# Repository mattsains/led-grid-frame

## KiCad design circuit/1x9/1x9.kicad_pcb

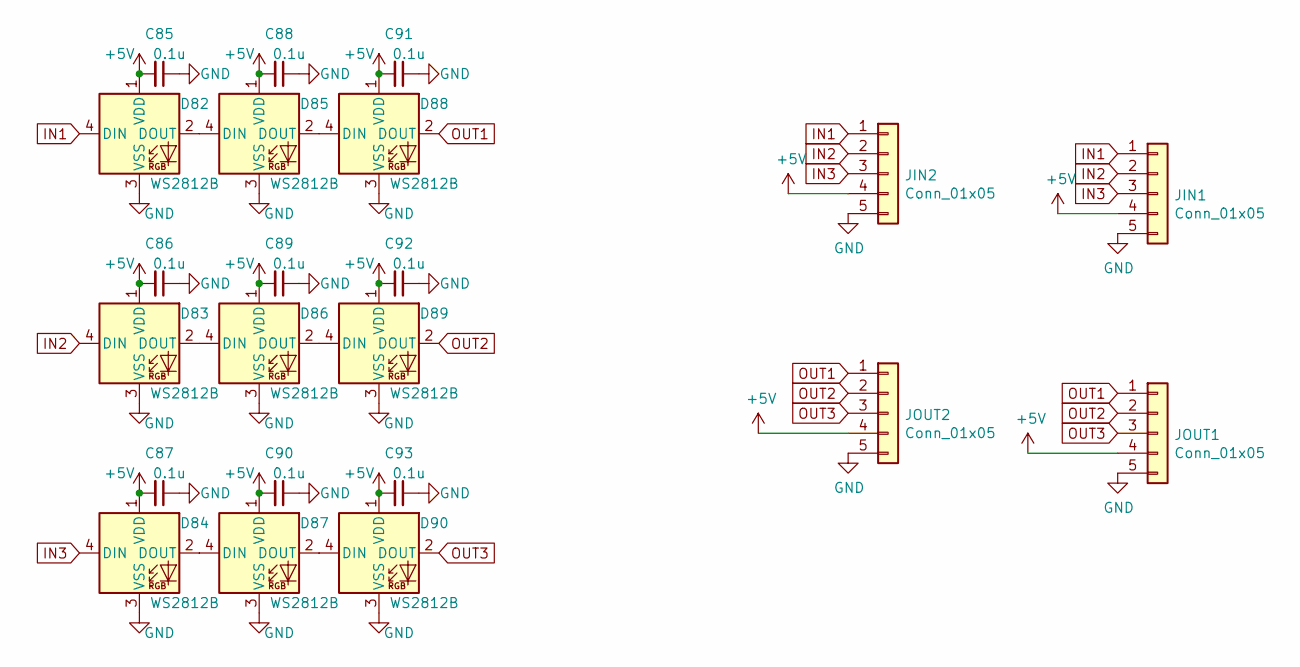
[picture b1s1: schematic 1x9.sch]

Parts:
C85, C86, C87, C88, C89, C90, C91, C92, C93: 0.1u; C_0805_2012Metric
D82, D83, D84, D85, D86, D87, D88, D89, D90: WS2812B; LED_WS2812B_PLCC4_5.0x5.0mm_P3.2mm
JIN1, JIN2: Conn_01x05; thick_header_01x05_3.3mm
JOUT1, JOUT3: Conn_01x05; thick_header_01x05_3.3mm

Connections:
+5V: C85.2, C86.2, C87.2, C88.2, C89.2, C90.2, C91.2, C92.2, C93.2, D82.1 (VDD), D83.1 (VDD), D84.1 (VDD), D85.1 (VDD), D86.1 (VDD), D87.1 (VDD), D88.1 (VDD), D89.1 (VDD), D90.1 (VDD), JIN1.4, JIN2.4, JOUT1.4; also elsewhere on the board
GND: C85.1, C86.1, C87.1, C88.1, C89.1, C90.1, C91.1, C92.1, C93.1, D82.3 (VSS), D83.3 (VSS), D84.3 (VSS), D85.3 (VSS), D86.3 (VSS), D87.3 (VSS), D88.3 (VSS), D89.3 (VSS), D90.3 (VSS), JIN1.5, JIN2.5, JOUT1.5; also elsewhere on the board
IN1: D82.4 (DIN), JIN1.1, JIN2.1
IN2: D83.4 (DIN), JIN1.2, JIN2.2
IN3: D84.4 (DIN), JIN1.3, JIN2.3
unnamed: D82.2 (DOUT), D85.4 (DIN)
unnamed: D83.2 (DOUT), D86.4 (DIN)
unnamed: D84.2 (DOUT), D87.4 (DIN)
unnamed: D85.2 (DOUT), D88.4 (DIN)
unnamed: D86.2 (DOUT), D89.4 (DIN)
unnamed: D87.2 (DOUT), D90.4 (DIN)
OUT1: D88.2 (DOUT), JOUT1.1; also elsewhere on the board
OUT2: D89.2 (DOUT), JOUT1.2; also elsewhere on the board
OUT3: D90.2 (DOUT), JOUT1.3; also elsewhere on the board

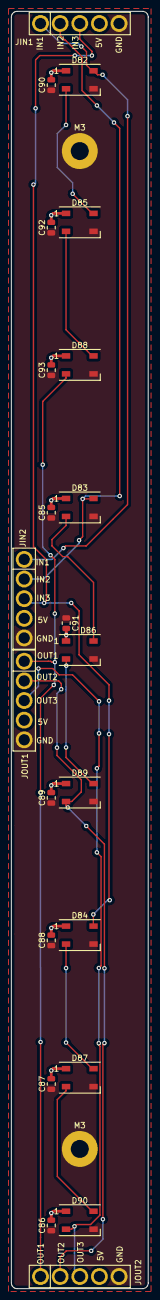
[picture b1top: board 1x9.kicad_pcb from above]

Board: 2 copper layers, 24.4 x 227.6 mm, 24 parts (0 on the bottom side), 14 nets.

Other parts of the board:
JOUT2: Conn_01x05; thick_header_01x05_3.3mm
M3, M3#2: MountingHole_3.2mm_M3_Pad

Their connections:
+5V: JOUT2.4; also elsewhere on the board
GND: JOUT2.5, M3.1, M3#2.1; also elsewhere on the board
OUT1: JOUT2.1; also elsewhere on the board
OUT2: JOUT2.2; also elsewhere on the board
OUT3: JOUT2.3; also elsewhere on the board

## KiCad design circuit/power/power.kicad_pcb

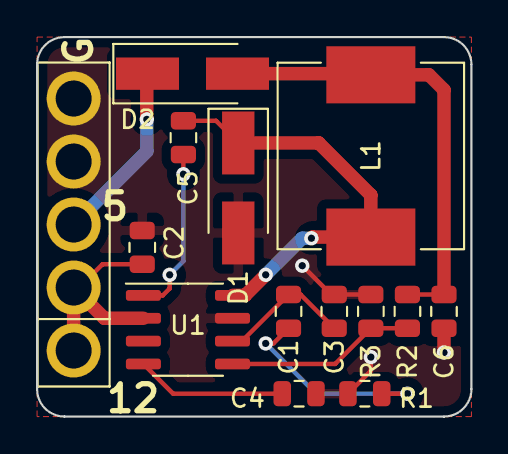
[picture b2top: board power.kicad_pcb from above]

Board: 2 copper layers, 24.1 x 21.1 mm, 14 parts (0 on the bottom side), 10 nets.

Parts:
C1: 1800p; C_0805_2012Metric
C2: 10u; C_0805_2012Metric
C3: 68p; C_0805_2012Metric
C4: 0.015u; C_0805_2012Metric
C5: 0.1u; C_0805_2012Metric
C6: 47u; C_0805_2012Metric
D1, D2: B240A; D_SMA_Handsoldering
JIN1: Conn_01x05; thick_header_01x05_3.3mm
L1: 22u; L_Vishay_IHLP-4040
R1: 21k; R_0805_2012Metric
R2: 10k; R_0805_2012Metric
R3: 1.91k; R_0805_2012Metric
U1: TPS54233; SOIC-8_3.9x4.9mm_P1.27mm

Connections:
+5V: D2.1, JIN1.3
+12V: C2.1, JIN1.1, JIN1.2, U1.2
GND: C2.2, C3.2, C4.2, C6.2, D1.2, JIN1.4, JIN1.5, R1.2, R3.2, U1.7
unnamed: C1.1, C3.1, U1.6
unnamed: C1.2, R1.1
unnamed: C4.1, U1.4
unnamed: C5.1, D1.1, L1.1, U1.8
unnamed: C5.2, U1.1
unnamed: C6.1, D2.2, L1.2, R2.1
unnamed: R2.2, R3.1, U1.5

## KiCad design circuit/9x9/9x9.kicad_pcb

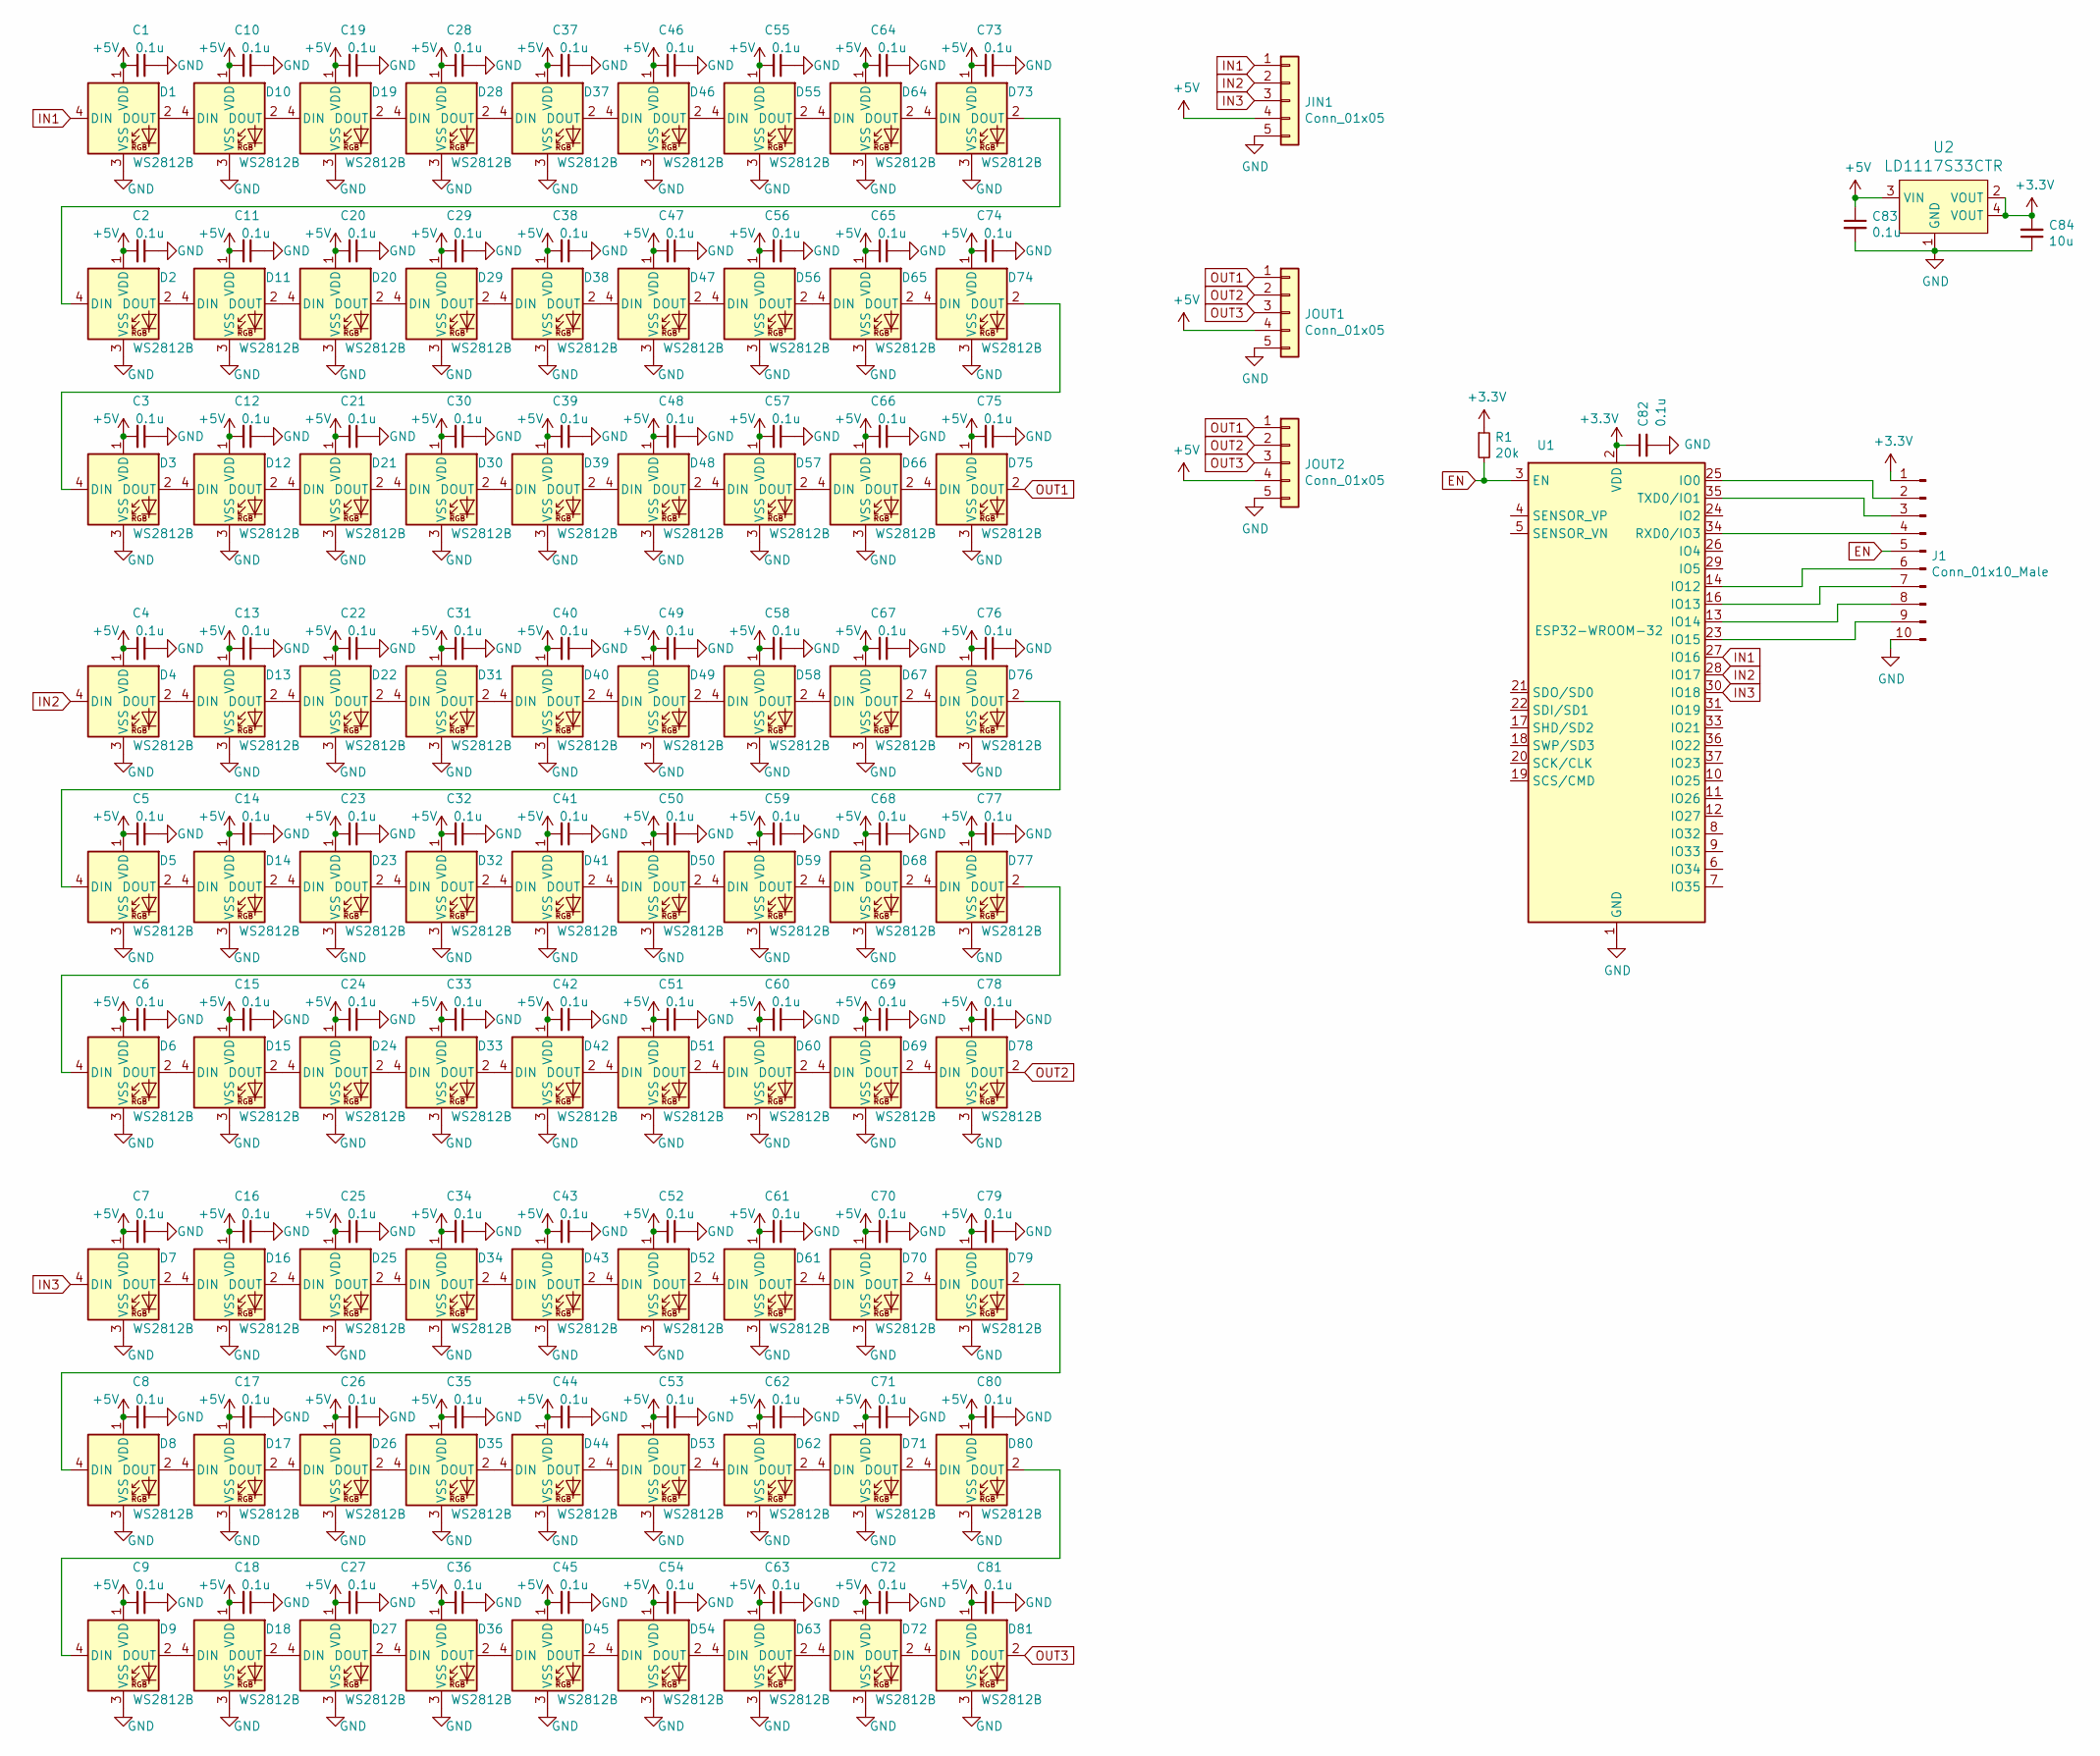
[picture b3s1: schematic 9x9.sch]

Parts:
C1, C2, C3, C4, C5, C6, C7, C8, C9, C10, C11, C12, C13, C14, C15, C16, C17, C18, C19, C20, C21, C22, C23, C24, C25, C26, C27, C28, C29, C30, C31, C32, C33, C34, C35, C36, C37, C38, C39, C40, C41, C42, C43, C44, C45, C46, C47, C48, C49, C50, C51, C52, C53, C54, C55, C56, C57, C58, C59, C60, C61, C62, C63, C64, C65, C66, C67, C68, C69, C70, C71, C72, C73, C74, C75, C76, C77, C78, C79, C80, C81, C82, C83: 0.1u; C_0805_2012Metric
C84: 10u; C_0805_2012Metric
D1, D2, D3, D4, D5, D6, D7, D8, D9, D10, D11, D12, D13, D14, D15, D16, D17, D18, D19, D20, D21, D22, D23, D24, D25, D26, D27, D28, D29, D30, D31, D32, D33, D34, D35, D36, D37, D38, D39, D40, D41, D42, D43, D44, D45, D46, D47, D48, D49, D50, D51, D52, D53, D54, D55, D56, D57, D58, D59, D60, D61, D62, D63, D64, D65, D66, D67, D68, D69, D70, D71, D72, D73, D74, D75, D76, D77, D78, D79, D80, D81: WS2812B; LED_WS2812B_PLCC4_5.0x5.0mm_P3.2mm
J1: Conn_01x10_Male; PinHeader_2x05_P2.54mm_Vertical
JIN1: Conn_01x05; thick_header_01x05_3.3mm
JOUT1, JOUT2: Conn_01x05; thick_header_01x05_3.3mm
R1: 20k; C_1206_3216Metric
U1: ESP32-WROOM-32
U2: LD1117S33CTR; SOT-223; MPN LD1117S33CTR; Digi-Key_PN 497-1241-1-ND

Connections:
+3V3: C82.1, C84.2, J1.1, R1.1, U1.2 (VDD), U2.2 (VOUT), U2.4 (VOUT)
+5V: C1.2, C2.2, C3.2, C4.2, C5.2, C6.2, C7.2, C8.2, C9.2, C10.2, C11.2, C12.2, C13.2, C14.2, C15.2, C16.2, C17.2, C18.2, C19.2, C20.2, C21.2, C22.2, C23.2, C24.2, C25.2, C26.2, C27.2, C28.2, C29.2, C30.2, C31.2, C32.2, C33.2, C34.2, C35.2, C36.2, C37.2, C38.2, C39.2, C40.2, C41.2, C42.2, C43.2, C44.2, C45.2, C46.2, C47.2, C48.2, C49.2, C50.2, C51.2, C52.2, C53.2, C54.2, C55.2, C56.2, C57.2, C58.2, C59.2, C60.2, C61.2, C62.2, C63.2, C64.2, C65.2, C66.2, C67.2, C68.2, C69.2, C70.2, C71.2, C72.2, C73.2, C74.2, C75.2, C76.2, C77.2, C78.2, C79.2, C80.2, C81.2, C83.1, D1.1 (VDD), D2.1 (VDD), D3.1 (VDD), D4.1 (VDD), D5.1 (VDD), D6.1 (VDD), D7.1 (VDD), D8.1 (VDD), D9.1 (VDD), D10.1 (VDD), D11.1 (VDD), D12.1 (VDD), D13.1 (VDD), D14.1 (VDD), D15.1 (VDD), D16.1 (VDD), D17.1 (VDD), D18.1 (VDD), D19.1 (VDD), D20.1 (VDD), D21.1 (VDD), D22.1 (VDD), D23.1 (VDD), D24.1 (VDD), D25.1 (VDD), D26.1 (VDD), D27.1 (VDD), D28.1 (VDD), D29.1 (VDD), D30.1 (VDD), D31.1 (VDD), D32.1 (VDD), D33.1 (VDD), D34.1 (VDD), D35.1 (VDD), D36.1 (VDD), D37.1 (VDD), D38.1 (VDD), D39.1 (VDD), D40.1 (VDD), D41.1 (VDD), D42.1 (VDD), D43.1 (VDD), D44.1 (VDD), D45.1 (VDD), D46.1 (VDD), D47.1 (VDD), D48.1 (VDD), D49.1 (VDD), D50.1 (VDD), D51.1 (VDD), D52.1 (VDD), D53.1 (VDD), D54.1 (VDD), D55.1 (VDD), D56.1 (VDD), D57.1 (VDD), D58.1 (VDD), D59.1 (VDD), D60.1 (VDD), D61.1 (VDD), D62.1 (VDD), D63.1 (VDD), D64.1 (VDD), D65.1 (VDD), D66.1 (VDD), D67.1 (VDD), D68.1 (VDD), D69.1 (VDD), D70.1 (VDD), D71.1 (VDD), D72.1 (VDD), D73.1 (VDD), D74.1 (VDD), D75.1 (VDD), D76.1 (VDD), D77.1 (VDD), D78.1 (VDD), D79.1 (VDD), D80.1 (VDD), D81.1 (VDD), JIN1.4, JOUT1.4, JOUT2.4, U2.3 (VIN)
EN: J1.5, R1.2, U1.3 (EN)
GND: C1.1, C2.1, C3.1, C4.1, C5.1, C6.1, C7.1, C8.1, C9.1, C10.1, C11.1, C12.1, C13.1, C14.1, C15.1, C16.1, C17.1, C18.1, C19.1, C20.1, C21.1, C22.1, C23.1, C24.1, C25.1, C26.1, C27.1, C28.1, C29.1, C30.1, C31.1, C32.1, C33.1, C34.1, C35.1, C36.1, C37.1, C38.1, C39.1, C40.1, C41.1, C42.1, C43.1, C44.1, C45.1, C46.1, C47.1, C48.1, C49.1, C50.1, C51.1, C52.1, C53.1, C54.1, C55.1, C56.1, C57.1, C58.1, C59.1, C60.1, C61.1, C62.1, C63.1, C64.1, C65.1, C66.1, C67.1, C68.1, C69.1, C70.1, C71.1, C72.1, C73.1, C74.1, C75.1, C76.1, C77.1, C78.1, C79.1, C80.1, C81.1, C82.2, C83.2, C84.1, D1.3 (VSS), D2.3 (VSS), D3.3 (VSS), D4.3 (VSS), D5.3 (VSS), D6.3 (VSS), D7.3 (VSS), D8.3 (VSS), D9.3 (VSS), D10.3 (VSS), D11.3 (VSS), D12.3 (VSS), D13.3 (VSS), D14.3 (VSS), D15.3 (VSS), D16.3 (VSS), D17.3 (VSS), D18.3 (VSS), D19.3 (VSS), D20.3 (VSS), D21.3 (VSS), D22.3 (VSS), D23.3 (VSS), D24.3 (VSS), D25.3 (VSS), D26.3 (VSS), D27.3 (VSS), D28.3 (VSS), D29.3 (VSS), D30.3 (VSS), D31.3 (VSS), D32.3 (VSS), D33.3 (VSS), D34.3 (VSS), D35.3 (VSS), D36.3 (VSS), D37.3 (VSS), D38.3 (VSS), D39.3 (VSS), D40.3 (VSS), D41.3 (VSS), D42.3 (VSS), D43.3 (VSS), D44.3 (VSS), D45.3 (VSS), D46.3 (VSS), D47.3 (VSS), D48.3 (VSS), D49.3 (VSS), D50.3 (VSS), D51.3 (VSS), D52.3 (VSS), D53.3 (VSS), D54.3 (VSS), D55.3 (VSS), D56.3 (VSS), D57.3 (VSS), D58.3 (VSS), D59.3 (VSS), D60.3 (VSS), D61.3 (VSS), D62.3 (VSS), D63.3 (VSS), D64.3 (VSS), D65.3 (VSS), D66.3 (VSS), D67.3 (VSS), D68.3 (VSS), D69.3 (VSS), D70.3 (VSS), D71.3 (VSS), D72.3 (VSS), D73.3 (VSS), D74.3 (VSS), D75.3 (VSS), D76.3 (VSS), D77.3 (VSS), D78.3 (VSS), D79.3 (VSS), D80.3 (VSS), D81.3 (VSS), J1.10, JIN1.5, JOUT1.5, JOUT2.5, U1.1 (GND), U1.15 (GND), U1.38 (GND), U2.1 (GND)
IN1: D1.4 (DIN), JIN1.1, U1.27 (IO16)
IN2: D4.4 (DIN), JIN1.2, U1.28 (IO17)
IN3: D7.4 (DIN), JIN1.3, U1.30 (IO18)
unnamed: D1.2 (DOUT), D10.4 (DIN)
unnamed: D2.4 (DIN), D73.2 (DOUT)
unnamed: D3.4 (DIN), D74.2 (DOUT)
unnamed: D5.4 (DIN), D76.2 (DOUT)
unnamed: D6.4 (DIN), D77.2 (DOUT)
unnamed: D10.2 (DOUT), D19.4 (DIN)
unnamed: D11.2 (DOUT), D20.4 (DIN)
unnamed: D2.2 (DOUT), D11.4 (DIN)
unnamed: D12.2 (DOUT), D21.4 (DIN)
unnamed: D3.2 (DOUT), D12.4 (DIN)
unnamed: D13.2 (DOUT), D22.4 (DIN)
unnamed: D4.2 (DOUT), D13.4 (DIN)
unnamed: D14.2 (DOUT), D23.4 (DIN)
unnamed: D5.2 (DOUT), D14.4 (DIN)
unnamed: D15.2 (DOUT), D24.4 (DIN)
unnamed: D6.2 (DOUT), D15.4 (DIN)
unnamed: D16.2 (DOUT), D25.4 (DIN)
unnamed: D7.2 (DOUT), D16.4 (DIN)
unnamed: D17.2 (DOUT), D26.4 (DIN)
unnamed: D8.2 (DOUT), D17.4 (DIN)
unnamed: D18.2 (DOUT), D27.4 (DIN)
unnamed: D9.2 (DOUT), D18.4 (DIN)
unnamed: D19.2 (DOUT), D28.4 (DIN)
unnamed: D20.2 (DOUT), D29.4 (DIN)
unnamed: D21.2 (DOUT), D30.4 (DIN)
unnamed: D22.2 (DOUT), D31.4 (DIN)
unnamed: D23.2 (DOUT), D32.4 (DIN)
unnamed: D24.2 (DOUT), D33.4 (DIN)
unnamed: D25.2 (DOUT), D34.4 (DIN)
unnamed: D26.2 (DOUT), D35.4 (DIN)
unnamed: D27.2 (DOUT), D36.4 (DIN)
unnamed: D28.2 (DOUT), D37.4 (DIN)
unnamed: D29.2 (DOUT), D38.4 (DIN)
unnamed: D30.2 (DOUT), D39.4 (DIN)
unnamed: D31.2 (DOUT), D40.4 (DIN)
unnamed: D32.2 (DOUT), D41.4 (DIN)
unnamed: D33.2 (DOUT), D42.4 (DIN)
unnamed: D34.2 (DOUT), D43.4 (DIN)
unnamed: D35.2 (DOUT), D44.4 (DIN)
unnamed: D36.2 (DOUT), D45.4 (DIN)
unnamed: D37.2 (DOUT), D46.4 (DIN)
unnamed: D38.2 (DOUT), D47.4 (DIN)
unnamed: D39.2 (DOUT), D48.4 (DIN)
unnamed: D40.2 (DOUT), D49.4 (DIN)
unnamed: D41.2 (DOUT), D50.4 (DIN)
unnamed: D42.2 (DOUT), D51.4 (DIN)
unnamed: D43.2 (DOUT), D52.4 (DIN)
unnamed: D44.2 (DOUT), D53.4 (DIN)
unnamed: D45.2 (DOUT), D54.4 (DIN)
unnamed: D46.2 (DOUT), D55.4 (DIN)
unnamed: D47.2 (DOUT), D56.4 (DIN)
unnamed: D48.2 (DOUT), D57.4 (DIN)
unnamed: D49.2 (DOUT), D58.4 (DIN)
unnamed: D50.2 (DOUT), D59.4 (DIN)
unnamed: D51.2 (DOUT), D60.4 (DIN)
unnamed: D52.2 (DOUT), D61.4 (DIN)
unnamed: D53.2 (DOUT), D62.4 (DIN)
unnamed: D54.2 (DOUT), D63.4 (DIN)
unnamed: D55.2 (DOUT), D64.4 (DIN)
unnamed: D56.2 (DOUT), D65.4 (DIN)
unnamed: D57.2 (DOUT), D66.4 (DIN)
unnamed: D58.2 (DOUT), D67.4 (DIN)
unnamed: D59.2 (DOUT), D68.4 (DIN)
unnamed: D60.2 (DOUT), D69.4 (DIN)
unnamed: D61.2 (DOUT), D70.4 (DIN)
unnamed: D62.2 (DOUT), D71.4 (DIN)
unnamed: D63.2 (DOUT), D72.4 (DIN)
unnamed: D64.2 (DOUT), D73.4 (DIN)
unnamed: D65.2 (DOUT), D74.4 (DIN)
unnamed: D66.2 (DOUT), D75.4 (DIN)
unnamed: D67.2 (DOUT), D76.4 (DIN)
unnamed: D68.2 (DOUT), D77.4 (DIN)
unnamed: D69.2 (DOUT), D78.4 (DIN)
unnamed: D70.2 (DOUT), D79.4 (DIN)
unnamed: D71.2 (DOUT), D80.4 (DIN)
unnamed: D72.2 (DOUT), D81.4 (DIN)
unnamed: D8.4 (DIN), D79.2 (DOUT)
unnamed: D9.4 (DIN), D80.2 (DOUT)
unnamed: J1.2, U1.25 (IO0)
unnamed: J1.3, U1.35 (TXD0/IO1)
unnamed: J1.4, U1.34 (RXD0/IO3)
unnamed: J1.6, U1.14 (IO12)
unnamed: J1.7, U1.16 (IO13)
unnamed: J1.8, U1.13 (IO14)
unnamed: J1.9, U1.23 (IO15)
OUT1: D75.2 (DOUT), JOUT1.1, JOUT2.1
OUT2: D78.2 (DOUT), JOUT1.2, JOUT2.2
OUT3: D81.2 (DOUT), JOUT1.3, JOUT2.3

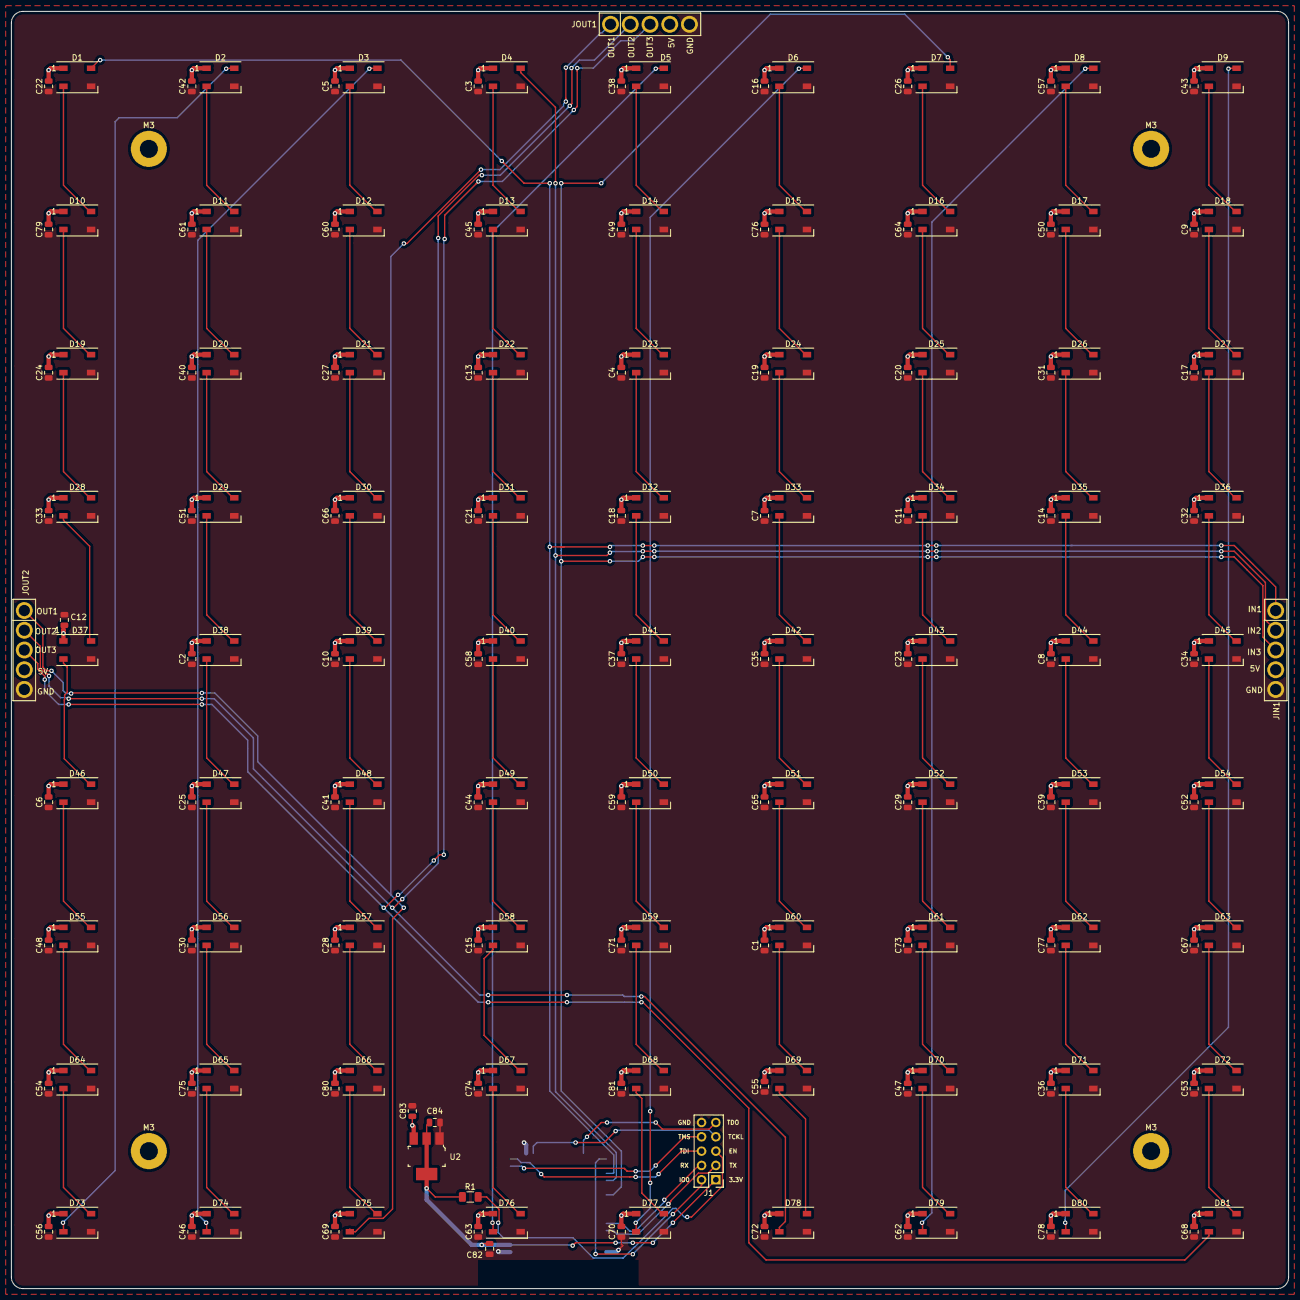
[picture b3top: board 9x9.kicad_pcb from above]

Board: 2 copper layers, 226.6 x 226.6 mm, 176 parts (1 on the bottom side), 95 nets.

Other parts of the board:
M3, M3#2, M3#3, M3#4: MountingHole_3.2mm_M3_Pad

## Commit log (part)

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2020-05-06 v1.1
2020-05-13 snapshot v1.1 and start firmware project
2020-05-16 LED code not working but not crashing either
2020-05-17 LEDs work
2020-05-21 falling rain animation on 9x9!
2020-05-30 18x9 panel
2020-05-30 hacky rain on 19x9
2021-03-06 second layer working
2021-03-06 adding encoder
2021-03-06 color wheel
2021-03-07 working!
2021-03-08 first web UI
2021-03-14 improved client code
2021-03-14 wip: improved firmware stability but still dies occasionally
2021-03-14 ball animation and comments for websocket handler
2021-05-12 Bump postcss from 8.2.7 to 8.2.15 in /client
    Bumps [postcss](https://github.com/postcss/postcss) from 8.2.7 to 8.2.15.
    - [Release notes](https://github.com/postcss/postcss/releases)
    - [Changelog](https://github.com/postcss/postcss/blob/main/CHANGELOG.md)
    - [Commits](https://github.com/postcss/postcss/compare/8.2.7...8.2.15)
2021-05-29 Bump dns-packet from 1.3.1 to 1.3.4 in /client
    Bumps [dns-packet](https://github.com/mafintosh/dns-packet) from 1.3.1 to 1.3.4.
    - [Release notes](https://github.com/mafintosh/dns-packet/releases)
    - [Changelog](https://github.com/mafintosh/dns-packet/blob/master/CHANGELOG.md)
    - [Commits](https://github.com/mafintosh/dns-packet/compare/v1.3.1...v1.3.4)
2021-05-31 Bump ws from 7.4.4 to 7.4.6 in /client
    Bumps [ws](https://github.com/websockets/ws) from 7.4.4 to 7.4.6.
    - [Release notes](https://github.com/websockets/ws/releases)
    - [Commits](https://github.com/websockets/ws/compare/7.4.4...7.4.6)
2021-08-13 Bump path-parse from 1.0.6 to 1.0.7 in /client
    Bumps [path-parse](https://github.com/jbgutierrez/path-parse) from 1.0.6 to 1.0.7.
    - [Release notes](https://github.com/jbgutierrez/path-parse/releases)
    - [Commits](https://github.com/jbgutierrez/path-parse/commits/v1.0.7)
    ---
    updated-dependencies:
    - dependency-name: path-parse
2021-10-06 Bump url-parse from 1.5.1 to 1.5.3 in /client
    Bumps [url-parse](https://github.com/unshiftio/url-parse) from 1.5.1 to 1.5.3.
    - [Release notes](https://github.com/unshiftio/url-parse/releases)
    - [Commits](https://github.com/unshiftio/url-parse/compare/1.5.1...1.5.3)
    ---
    updated-dependencies:
    - dependency-name: url-parse
2021-12-08 it works!
2021-12-08 Displays scrolling emoji
2021-12-12 WIP tetris
2021-12-12 remove bearer token from git
2021-12-13 tetris game 90% there
2021-12-13 typos
2022-02-14 Bump follow-redirects from 1.13.3 to 1.14.8 in /client
    Bumps [follow-redirects](https://github.com/follow-redirects/follow-redirects) from 1.13.3 to 1.14.8.
    - [Release notes](https://github.com/follow-redirects/follow-redirects/releases)
    - [Commits](https://github.com/follow-redirects/follow-redirects/compare/v1.13.3...v1.14.8)
    ---
    updated-dependencies:
    - dependency-name: follow-redirects
2022-02-19 Bump url-parse from 1.5.3 to 1.5.7 in /client
    Bumps [url-parse](https://github.com/unshiftio/url-parse) from 1.5.3 to 1.5.7.
    - [Release notes](https://github.com/unshiftio/url-parse/releases)
    - [Commits](https://github.com/unshiftio/url-parse/compare/1.5.3...1.5.7)
    ---
    updated-dependencies:
    - dependency-name: url-parse
2022-02-26 Bump url-parse from 1.5.7 to 1.5.10 in /client
    Bumps [url-parse](https://github.com/unshiftio/url-parse) from 1.5.7 to 1.5.10.
    - [Release notes](https://github.com/unshiftio/url-parse/releases)
    - [Commits](https://github.com/unshiftio/url-parse/compare/1.5.7...1.5.10)
    ---
    updated-dependencies:
    - dependency-name: url-parse
2022-02-26 Bump browserslist from 4.16.3 to 4.19.3 in /client
    Bumps [browserslist](https://github.com/browserslist/browserslist) from 4.16.3 to 4.19.3.
    - [Release notes](https://github.com/browserslist/browserslist/releases)
    - [Changelog](https://github.com/browserslist/browserslist/blob/main/CHANGELOG.md)
    - [Commits](https://github.com/browserslist/browserslist/compare/4.16.3...4.19.3)
    ---
    updated-dependencies:
2022-02-26 Bump dns-packet from 1.3.1 to 1.3.4 in /client
    Bumps [dns-packet](https://github.com/mafintosh/dns-packet) from 1.3.1 to 1.3.4.
    - [Release notes](https://github.com/mafintosh/dns-packet/releases)
    - [Changelog](https://github.com/mafintosh/dns-packet/blob/master/CHANGELOG.md)
    - [Commits](https://github.com/mafintosh/dns-packet/compare/v1.3.1...v1.3.4)
    ---
    updated-dependencies:
2022-02-26 Bump nanoid from 3.1.20 to 3.3.1 in /client
    Bumps [nanoid](https://github.com/ai/nanoid) from 3.1.20 to 3.3.1.
    - [Release notes](https://github.com/ai/nanoid/releases)
    - [Changelog](https://github.com/ai/nanoid/blob/main/CHANGELOG.md)
    - [Commits](https://github.com/ai/nanoid/compare/3.1.20...3.3.1)
    ---
    updated-dependencies:
2022-03-27 empty app
2022-03-28 first poc game of life
2022-03-29 Bump minimist from 1.2.5 to 1.2.6 in /client
    Bumps [minimist](https://github.com/substack/minimist) from 1.2.5 to 1.2.6.
    - [Release notes](https://github.com/substack/minimist/releases)
    - [Commits](https://github.com/substack/minimist/compare/1.2.5...1.2.6)
    ---
    updated-dependencies:
    - dependency-name: minimist
2022-04-29 Bump async from 2.6.3 to 2.6.4 in /client
    Bumps [async](https://github.com/caolan/async) from 2.6.3 to 2.6.4.
    - [Release notes](https://github.com/caolan/async/releases)
    - [Changelog](https://github.com/caolan/async/blob/v2.6.4/CHANGELOG.md)
    - [Commits](https://github.com/caolan/async/compare/v2.6.3...v2.6.4)
    ---
    updated-dependencies:
2022-07-20 Bump terser from 5.6.0 to 5.14.2 in /client
    Bumps [terser](https://github.com/terser/terser) from 5.6.0 to 5.14.2.
    - [Release notes](https://github.com/terser/terser/releases)
    - [Changelog](https://github.com/terser/terser/blob/master/CHANGELOG.md)
    - [Commits](https://github.com/terser/terser/commits)
    ---
    updated-dependencies:
2022-11-08 Bump loader-utils from 1.4.0 to 1.4.1 in /client
    Bumps [loader-utils](https://github.com/webpack/loader-utils) from 1.4.0 to 1.4.1.
    - [Release notes](https://github.com/webpack/loader-utils/releases)
    - [Changelog](https://github.com/webpack/loader-utils/blob/v1.4.1/CHANGELOG.md)
    - [Commits](https://github.com/webpack/loader-utils/compare/v1.4.0...v1.4.1)
    ---
    updated-dependencies:
2022-11-09 Bump ansi-html and webpack-dev-server in /client
    Removes [ansi-html](https://github.com/Tjatse/ansi-html). It's no longer used after updating ancestor dependency [webpack-dev-server](https://github.com/webpack/webpack-dev-server). These dependencie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
    Removes `ansi-html`
    Updates `webpack-dev-server` from 3.11.2 to 3.11.3
    - [Release notes](https://github.com/webpack/webpack-dev-server/releases)
    - [Changelog](https://github.com/webpack/webpack-dev-server/blob/v3.11.3/CHANGELOG.md)
    - [Commits](https://github.com/webpack/webpack-dev-server/compare/v3.11.2...v3.11.3)
2022-11-09 Bump glob-parent, chokidar and webpack-dev-server in /client
    Bumps [glob-parent](https://github.com/gulpjs/glob-parent) to 5.1.2 and updates ancestor dependencies [glob-parent](https://github.com/gulpjs/glob-parent), [chokidar](https://github.com/paulmillr/cho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
    Updates `glob-parent` from 3.1.0 to 5.1.2
    - [Release notes](https://github.com/gulpjs/glob-parent/releases)
    - [Changelog](https://github.com/gulpjs/glob-parent/blob/main/CHANGELOG.md)
    - [Commits](https://github.com/gulpjs/glob-parent/compare/v3.1.0...v5.1.2)
    Updates `chokidar` from 2.1.8 to 3.5.3
2022-11-18 Bump loader-utils from 1.4.1 to 1.4.2 in /client
    Bumps [loader-utils](https://github.com/webpack/loader-utils) from 1.4.1 to 1.4.2.
    - [Release notes](https://github.com/webpack/loader-utils/releases)
    - [Changelog](https://github.com/webpack/loader-utils/blob/v1.4.2/CHANGELOG.md)
    - [Commits](https://github.com/webpack/loader-utils/compare/v1.4.1...v1.4.2)
    ---
    updated-dependencies:
2022-12-07 Bump decode-uri-component from 0.2.0 to 0.2.2 in /client
    Bumps [decode-uri-component](https://github.com/SamVerschueren/decode-uri-component) from 0.2.0 to 0.2.2.
    - [Release notes](https://github.com/SamVerschueren/decode-uri-component/releases)
    - [Commits](https://github.com/SamVerschueren/decode-uri-component/compare/v0.2.0...v0.2.2)
    ---
    updated-dependencies:
    - dependency-name: decode-uri-component
2023-01-07 Bump json5 from 1.0.1 to 1.0.2 in /client
    Bumps [json5](https://github.com/json5/json5) from 1.0.1 to 1.0.2.
    - [Release notes](https://github.com/json5/json5/releases)
    - [Changelog](https://github.com/json5/json5/blob/main/CHANGELOG.md)
    - [Commits](https://github.com/json5/json5/compare/v1.0.1...v1.0.2)
    ---
    updated-dependencies:
2023-03-14 Bump webpack from 5.24.3 to 5.76.0 in /client
    Bumps [webpack](https://github.com/webpack/webpack) from 5.24.3 to 5.76.0.
    - [Release notes](https://github.com/webpack/webpack/releases)
    - [Commits](https://github.com/webpack/webpack/compare/v5.24.3...v5.76.0)
    ---
    updated-dependencies:
    - dependency-name: webpack
2023-10-08 Bump postcss from 8.4.7 to 8.4.31 in /client
    Bumps [postcss](https://github.com/postcss/postcss) from 8.4.7 to 8.4.31.
    - [Release notes](https://github.com/postcss/postcss/releases)
    - [Changelog](https://github.com/postcss/postcss/blob/main/CHANGELOG.md)
    - [Commits](https://github.com/postcss/postcss/compare/8.4.7...8.4.31)
    ---
    updated-dependencies:
2024-01-10 Bump follow-redirects from 1.15.2 to 1.15.4 in /client
    Bumps [follow-redirects](https://github.com/follow-redirects/follow-redirects) from 1.15.2 to 1.15.4.
    - [Release notes](https://github.com/follow-redirects/follow-redirects/releases)
    - [Commits](https://github.com/follow-redirects/follow-redirects/compare/v1.15.2...v1.15.4)
    ---
    updated-dependencies:
    - dependency-name: follow-redirects
2024-02-27 Bump es5-ext from 0.10.53 to 0.10.63 in /client
    Bumps [es5-ext](https://github.com/medikoo/es5-ext) from 0.10.53 to 0.10.63.
    - [Release notes](https://github.com/medikoo/es5-ext/releases)
    - [Changelog](https://github.com/medikoo/es5-ext/blob/main/CHANGELOG.md)
    - [Commits](https://github.com/medikoo/es5-ext/compare/v0.10.53...v0.10.63)
    ---
    updated-dependencies:
2024-03-16 Bump follow-redirects from 1.15.4 to 1.15.6 in /client
    Bumps [follow-redirects](https://github.com/follow-redirects/follow-redirects) from 1.15.4 to 1.15.6.
    - [Release notes](https://github.com/follow-redirects/follow-redirects/releases)
    - [Commits](https://github.com/follow-redirects/follow-redirects/compare/v1.15.4...v1.15.6)
    ---
    updated-dependencies:
    - dependency-name: follow-redirects
2024-03-28 Bump express from 4.18.2 to 4.19.2 in /client
    Bumps [express](https://github.com/expressjs/express) from 4.18.2 to 4.19.2.
    - [Release notes](https://github.com/expressjs/express/releases)
    - [Changelog](https://github.com/expressjs/express/blob/master/History.md)
    - [Commits](https://github.com/expressjs/express/compare/4.18.2...4.19.2)
    ---
    updated-dependencies:
2024-06-17 Bump ws from 7.5.7 to 7.5.10 in /client
    Bumps [ws](https://github.com/websockets/ws) from 7.5.7 to 7.5.10.
    - [Release notes](https://github.com/websockets/ws/releases)
    - [Commits](https://github.com/websockets/ws/compare/7.5.7...7.5.10)
    ---
    updated-dependencies:
    - dependency-name: ws
